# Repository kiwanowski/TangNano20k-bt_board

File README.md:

# TangNano20k-bt_board
a bluetooth game controller board for Tang Nano 20k

## Usage
It can be used with NESTang - https://github.com/nand2mario/nestang
## Credits
The board is based on BlueRetro - https://github.com/darthcloud/BlueRetro

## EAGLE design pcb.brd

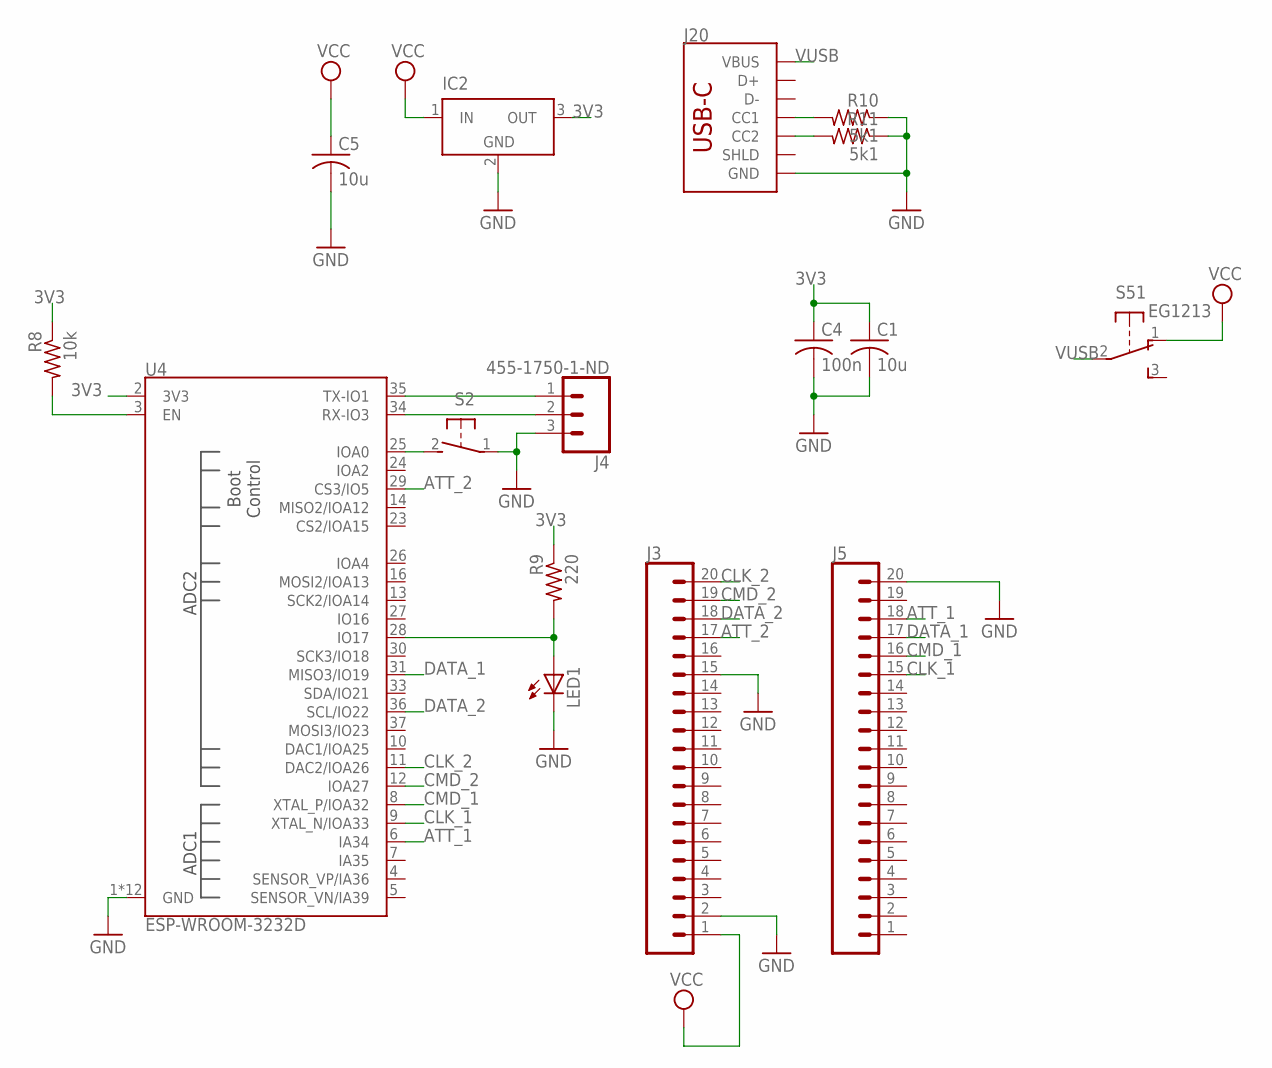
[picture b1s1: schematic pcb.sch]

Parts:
C1, C5: 10u; C0805
C4: 100n; C0805
IC2: LT1129CST5; SOT223
J3, J5: CONN_20; 1X20
J4: 455-1750-1-ND; 1X03
J20: USB_C_2-LAYER_PADS; USB-C-16P-2LAYER-PADS
LED1: LEDCHIP-LED0805; CHIP-LED0805
R8: 10k; R0805
R9: 220; R0805
R10, R11: 5k1; R0805
S2: 31-XX; B3F-31XX
S5: EG1213
U4: ESP-WROOM-3232D; ESP-WROOM-32D

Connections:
3V3: C1.1, C4.1, IC2.3 (OUT), R8.1, R9.1, U4.2 (3V3)
ATT_1: J5.18, U4.6 (IA34)
ATT_2: J3.17, U4.29 (CS3/IO5)
CLK_1: J5.15, U4.9 (XTAL_N/IOA33)
CLK_2: J3.20, U4.11 (DAC2/IOA26)
CMD_1: J5.16, U4.8 (XTAL_P/IOA32)
CMD_2: J3.19, U4.12 (IOA27)
DATA_1: J5.17, U4.31 (MISO3/IO19)
DATA_2: J3.18, U4.36 (SCL/IO22)
GND: C1.2, C4.2, C5.2, IC2.2 (GND), IC2.4 (GND), J3.2, J3.15, J4.3, J5.20, J20.GND, J20.GND2 (GND), LED1.C, R10.1, R11.1, S2.1, U4.1 (GND), U4.15 (GND), U4.38 (GND), U4.GND, U4.GNDT1 (GND), U4.GNDT2 (GND), U4.GNDT3 (GND), U4.GNDT4 (GND), U4.GNDT5 (GND), U4.GNDT6 (GND), U4.GNDT7 (GND), U4.GNDT8 (GND)
unnamed: R8.2, U4.3 (EN)
unnamed: LED1.A, R9.2, U4.28 (IO17)
unnamed: J20.A5 (CC1), R10.2
unnamed: J20.B5 (CC2), R11.2
unnamed: S2.2 (S), U4.25 (IOA0)
RX: J4.2, U4.34 (RX-IO3)
TX: J4.1, U4.35 (TX-IO1)
VCC: C5.1, IC2.1 (IN), J3.1, S5.1 (O)
VUSB: J20.VBUS1 (VBUS), J20.VBUS2 (VBUS), S5.2

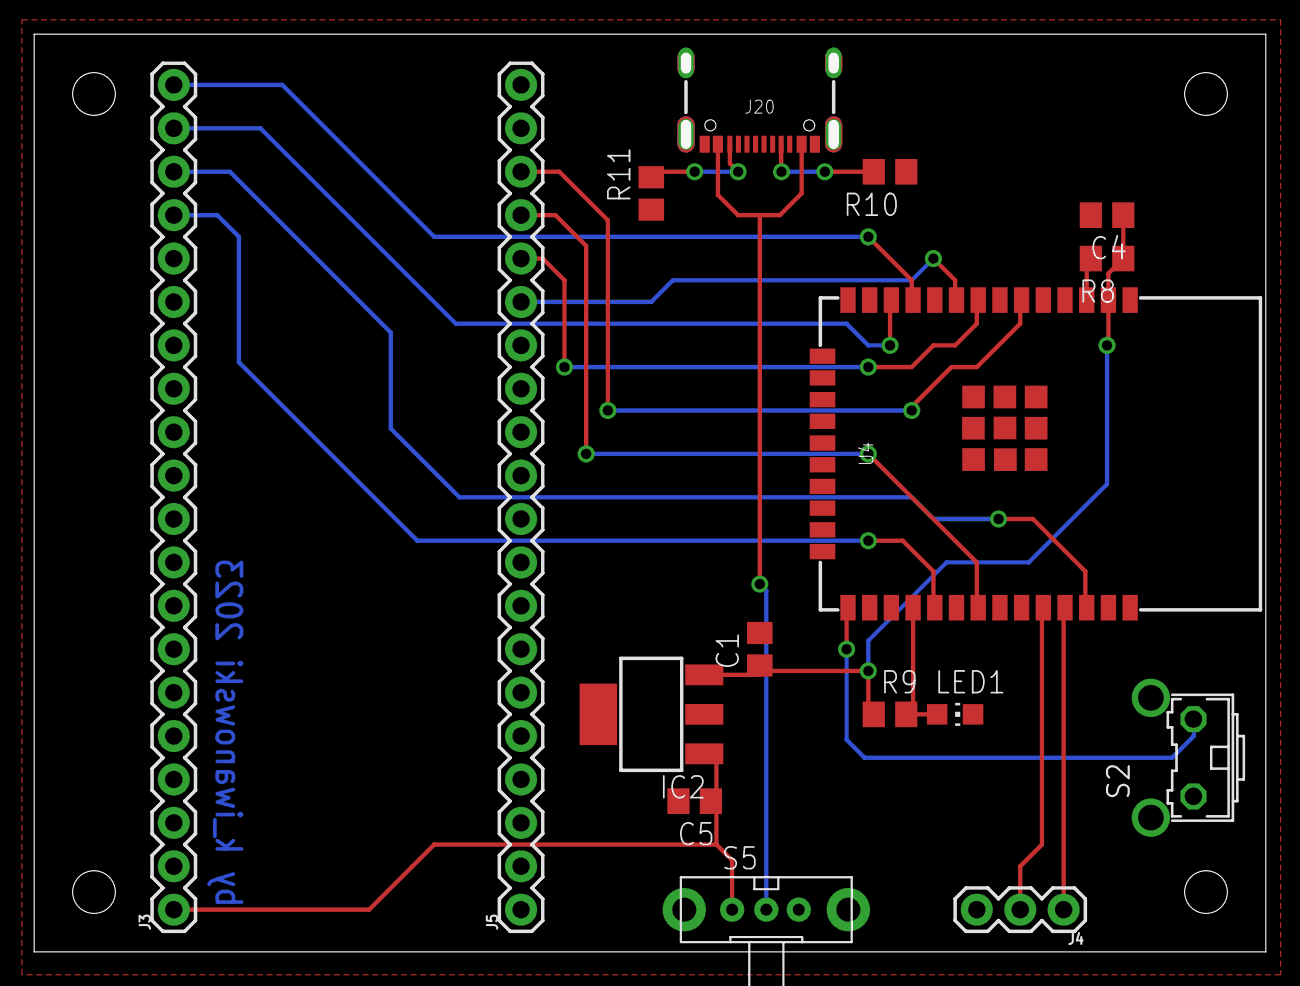
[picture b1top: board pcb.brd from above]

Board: 2 copper layers, 71.5 x 53.1 mm, 16 parts (0 on the bottom side), 19 nets.

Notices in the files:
parts and their libraries:
SparkFun-Connectors: Licensing: Creative Commons ShareAlike 4.0 International - https://creativecommons.org/licenses/by-sa/4.0
